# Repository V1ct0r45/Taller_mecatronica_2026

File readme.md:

## 1. Construcción Inicial (Solo la primera vez)
```bash
sudo docker compose build
```

## 2. Iniciar el Entorno
```bash
sudo docker compose up -d
```

## 3. Entrar a la Terminal de Ubuntu
```bash
sudo docker exec -it taller_torreta bash
```

## 4. Compilar Código ROS 2 (Dentro de Ubuntu)
```bash
cd ros2_ws
colcon build
source install/setup.bash
```

## 5. Abrir Simuladores (Dentro de Ubuntu)
Escribe cualquiera de estos comandos y presiona Enter:
* `simulide`
* `freecad`
* `kicad`
* `pio`
* `rviz2`
* `gz sim`

## 6. Apagar el Entorno (Al terminar el taller)
Desde tu terminal principal (fuera de Ubuntu), ejecuta:
```bash
sudo docker compose down
```

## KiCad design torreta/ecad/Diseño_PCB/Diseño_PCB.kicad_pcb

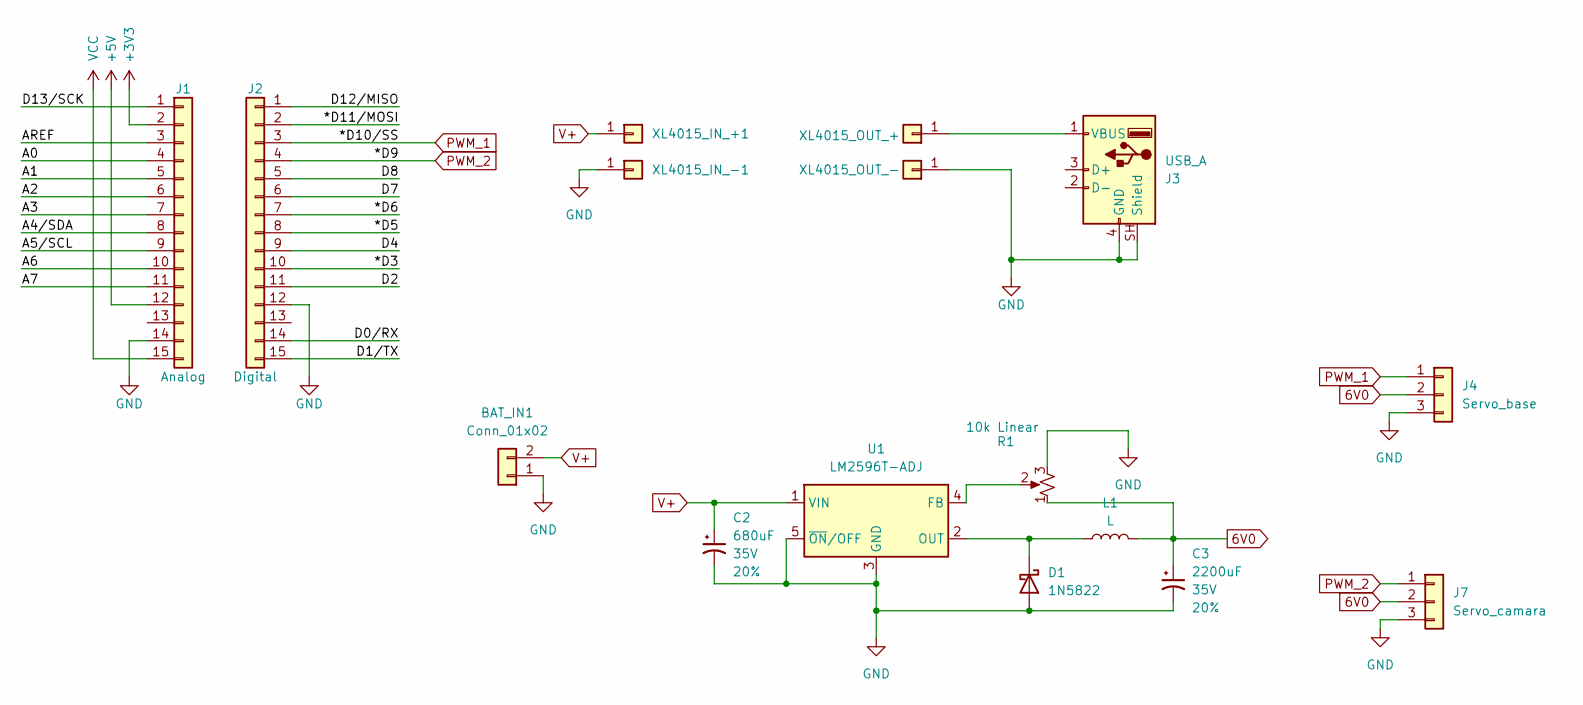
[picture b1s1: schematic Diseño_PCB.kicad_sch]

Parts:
BAT_IN1: Conn_01x02; TerminalBlock_CUI_TB007-508-02_1x02_P5.08mm_Horizontal
C2: 680uF; CP_Radial_D10.0mm_P5.00mm; Voltage 35V; Tolerance 20%
C3: 2200uF; CP_Radial_D16.0mm_P7.50mm; Voltage 35V; Tolerance 20%
D1: 1N5822; D_DO-201AD_P15.24mm_Horizontal
J1: Analog; PinSocket_1x15_P2.54mm_Vertical
J2: Digital; PinSocket_1x15_P2.54mm_Vertical
J3: USB_A; USB_A_Molex_67643_Horizontal
J4: Servo_base; PinSocket_1x03_P2.54mm_Vertical
J5: XL4015_OUT_-; PinSocket_1x01_P2.54mm_Vertical
J6: XL4015_OUT_+; PinSocket_1x01_P2.54mm_Vertical
J7: Servo_camara; PinSocket_1x03_P2.54mm_Vertical
L1: L; L_Radial_D10.5mm_P5.00mm_Abacron_AISR-01
R1: 10k Linear; Potentiometer_Bourns_3296W_Vertical
U1: LM2596T-ADJ; TO-220-5_P3.4x3.7mm_StaggerOdd_Lead3.8mm_Vertical
XL4015_IN_+1, XL4015_IN_-1: PinSocket_1x01_P2.54mm_Vertical

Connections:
6V0: C3.1, J4.2, J7.2, L1.2, R1.1
+3V3: J1.2
+5V: J1.12
/*D3: J2.10
/*D5: J2.8
/*D6: J2.7
/*D11/MOSI: J2.2
/A0: J1.4
/A1: J1.5
/A2: J1.6
/A3: J1.7
/A4/SDA: J1.8
/A5/SCL: J1.9
/A6: J1.10
/A7: J1.11
/AREF: J1.3
/D0/RX: J2.14
/D1/TX: J2.15
/D2: J2.11
/D4: J2.9
/D7: J2.6
/D8: J2.5
/D12/MISO: J2.1
/D13/SCK: J1.1
GND: BAT_IN1.1, C2.2, C3.2, D1.2 (A), J1.14, J2.12, J3.4 (GND), J3.SH (Shield), J4.3, J5.1 (Pin_1_1), J7.3, R1.3, U1.3 (GND), U1.5 (~ON/OFF), XL4015_IN_-1.1 (Pin_1_1)
unnamed: D1.1 (K), L1.1, U1.2 (OUT)
unnamed: J3.1 (VBUS), J6.1 (Pin_1_1)
unnamed: R1.2 (2_2), U1.4 (FB)
PWM_1: J2.3, J4.1
PWM_2: J2.4, J7.1
V+: BAT_IN1.2, C2.1, U1.1 (VIN), XL4015_IN_+1.1 (Pin_1_1)
VCC: J1.15

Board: 2 copper layers, 20 parts (4 on the bottom side), 8 nets, no tracks yet.

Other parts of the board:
MH1, MH2, MH3, MH4: MountingHole_65mil
